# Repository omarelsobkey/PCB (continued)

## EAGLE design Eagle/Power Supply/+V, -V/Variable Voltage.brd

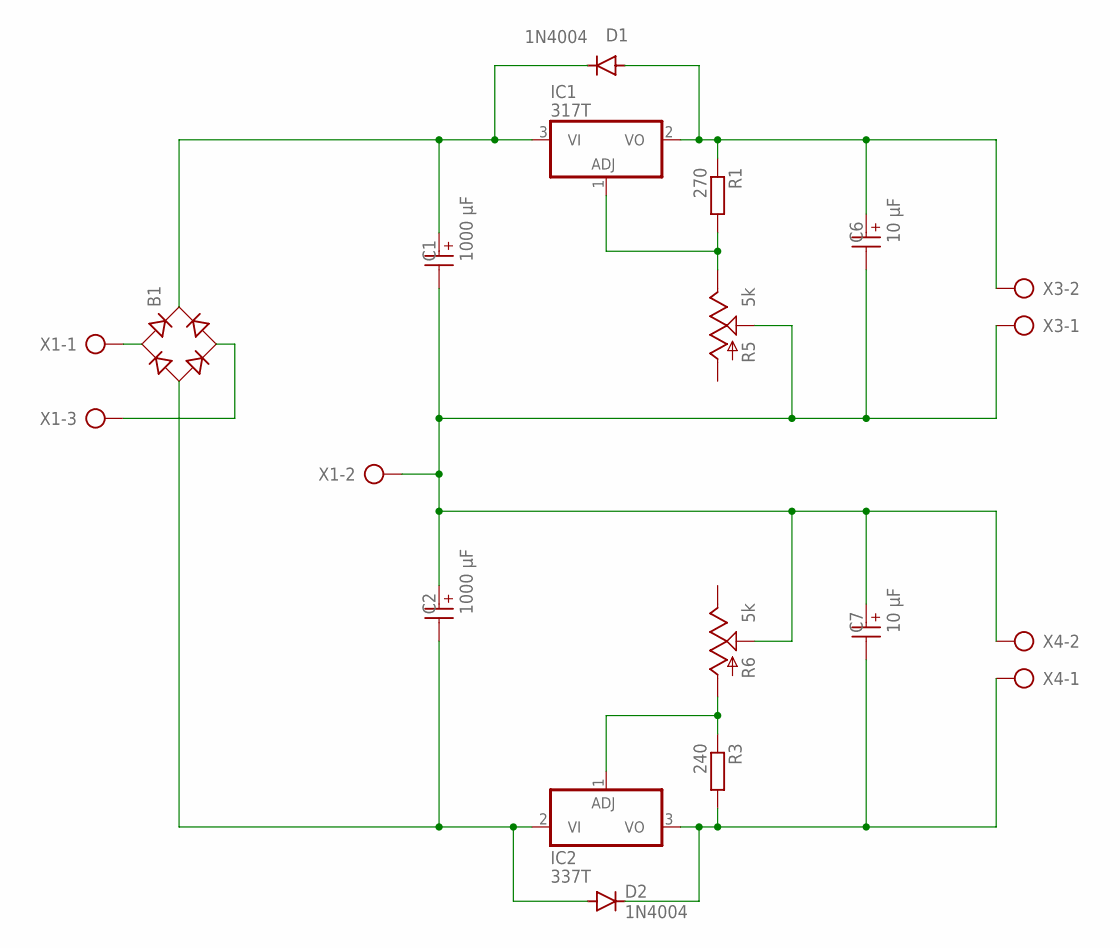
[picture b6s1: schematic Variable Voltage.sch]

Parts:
B1: RB1A
C1, C2: 1000 µF; WCAP-ATG8_10X12.5(DXL)
C6, C7: 10 µF; WCAP-ATG8_5X11(DXL)
D1, D2: 1N4004; DO41-10
IC1: 317T; TO220H
IC2: 337T; TO220H
R1: 270; 0204/7
R3: 240; 0204/7
R5, R6: 5k; CA9V
X1: AK300/3
X3, X4: AK300/2

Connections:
GND: C1.2 (-), C2.1 (+), C6.2 (-), C7.1 (+), R5.S, R6.S, X1.2, X3.1, X4.2
unnamed: B1.AC1, X1.1
unnamed: B1.AC2, X1.3
unnamed: B1.+, C1.1 (+), D1.C, IC1.3 (VI)
unnamed: B1.-, C2.2 (-), D2.A, IC2.2 (VI)
unnamed: IC2.1 (ADJ), R3.1, R6.A
unnamed: C7.2 (-), D2.C, IC2.3 (VO), R3.2, X4.1
unnamed: C6.1 (+), D1.A, IC1.2 (VO), R1.1, X3.2
unnamed: IC1.1 (ADJ), R1.2, R5.E

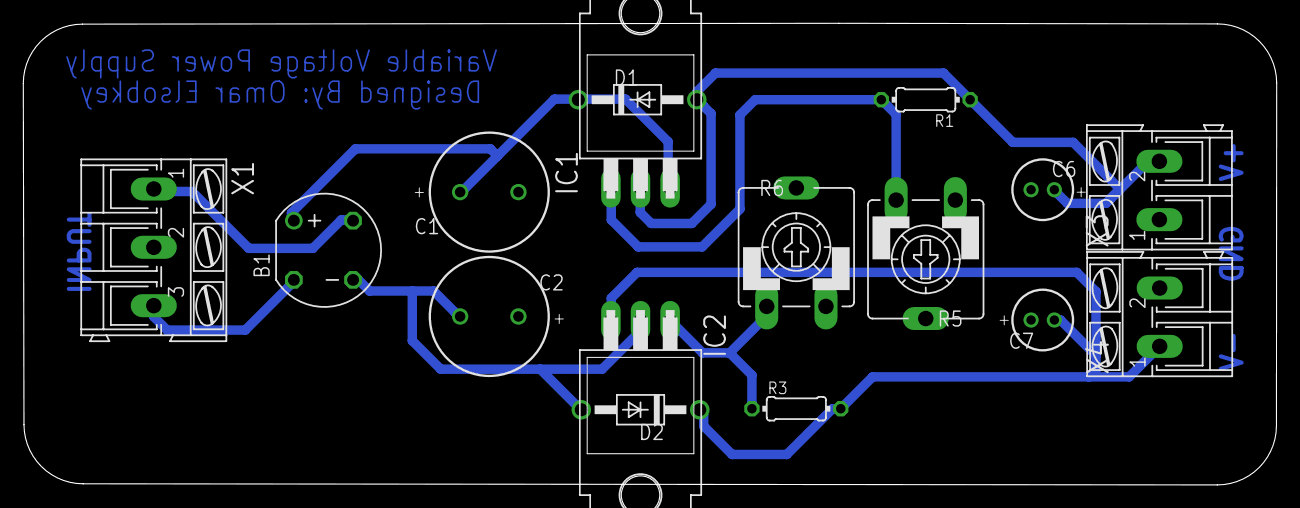
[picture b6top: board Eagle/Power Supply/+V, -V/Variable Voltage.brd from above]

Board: 2 copper layers, 107.5 x 39.6 mm, 16 parts (0 on the bottom side), 9 nets.

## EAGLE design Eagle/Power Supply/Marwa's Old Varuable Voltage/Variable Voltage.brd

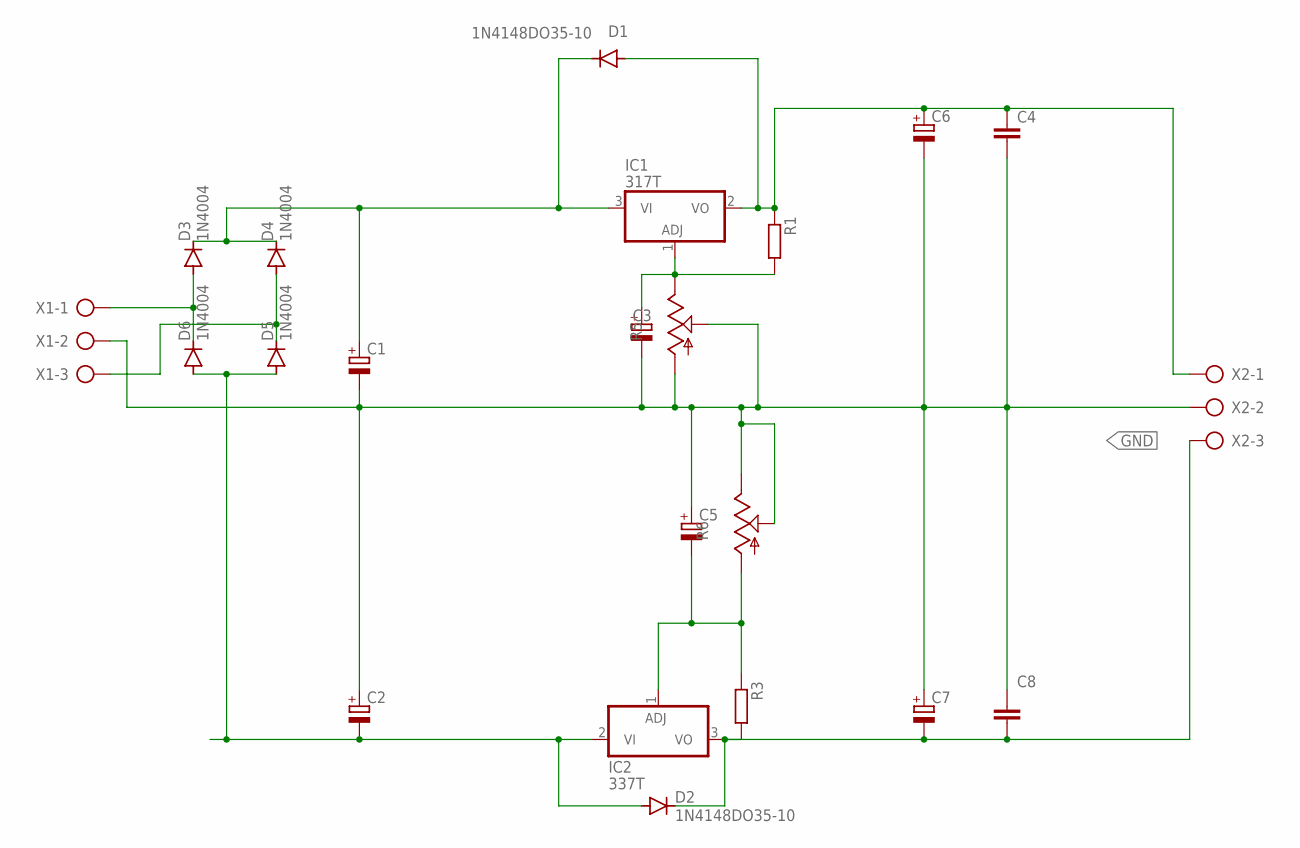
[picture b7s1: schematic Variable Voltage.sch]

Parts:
C1, C2: CPOL-EUE5-8.5; E5-8,5
C3, C5: CPOL-EUE2-4; E2-4
C4, C8: C2,5-3; C2.5-3
C6, C7: CPOL-EUE2.5-4V; E2,5RE
D1, D2: 1N4148DO35-10; DO35-10
D3, D4, D5, D6: 1N4004; DO41-10
IC1: 317T; TO220H
IC2: 337T; TO220H
R1, R3: R-EU_0204/7; 0204/7
R5, R6: TRIM_US-B25V; B25V
X1, X2: AK300/3

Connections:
GND: C1.-, C2.+, C3.-, C4.2, C5.+, C6.-, C7.+, C8.1, R5.A, R5.S, R6.E, R6.S, X1.2, X2.2
unnamed: D3.A, D6.C, X1.1
unnamed: D4.A, D5.C, X1.3
unnamed: C1.+, D1.C, D3.C, D4.C, IC1.3 (VI)
unnamed: C2.-, D2.A, D5.A, D6.A, IC2.2 (VI)
unnamed: C3.+, IC1.1 (ADJ), R1.2, R5.E
unnamed: C5.-, IC2.1 (ADJ), R3.1, R6.A
unnamed: C4.1, C6.+, D1.A, IC1.2 (VO), R1.1, X2.1
unnamed: C7.-, C8.2, D2.C, IC2.3 (VO), R3.2, X2.3

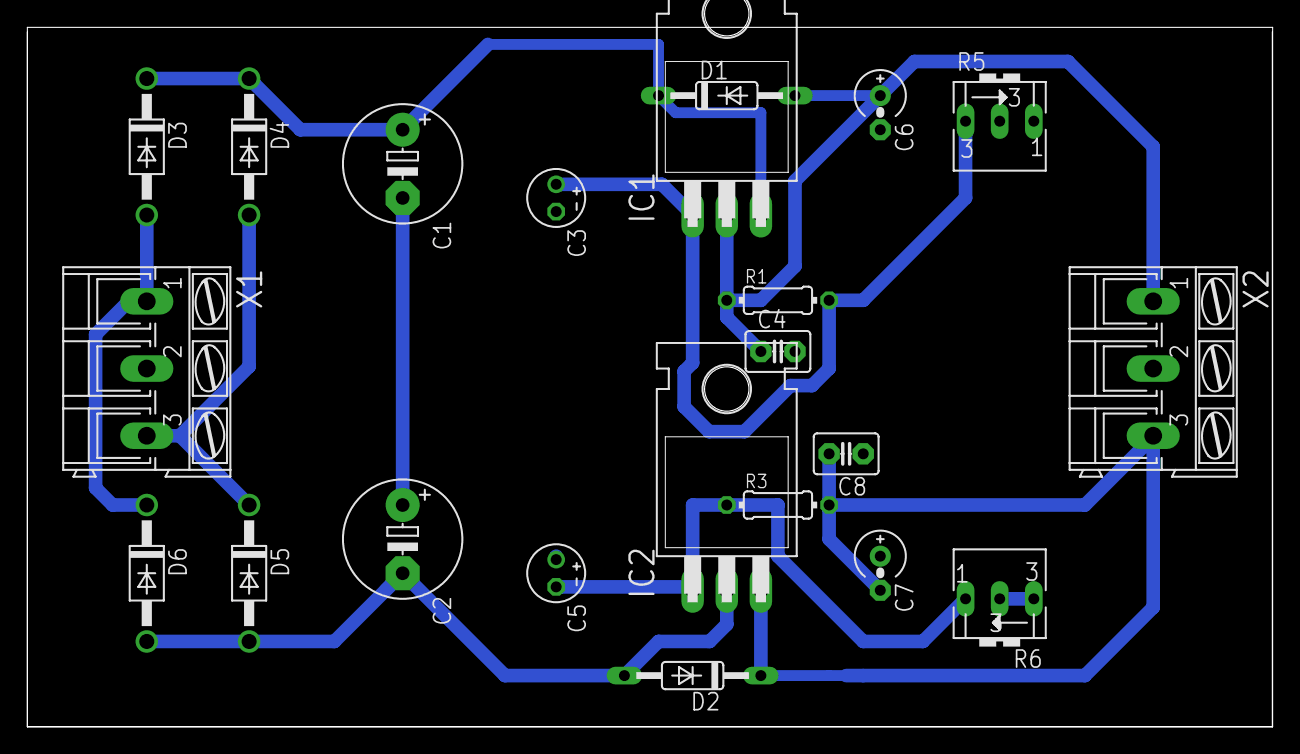
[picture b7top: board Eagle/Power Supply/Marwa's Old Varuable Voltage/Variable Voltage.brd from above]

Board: 2 copper layers, 92.7 x 52.1 mm, 22 parts (0 on the bottom side), 9 nets.

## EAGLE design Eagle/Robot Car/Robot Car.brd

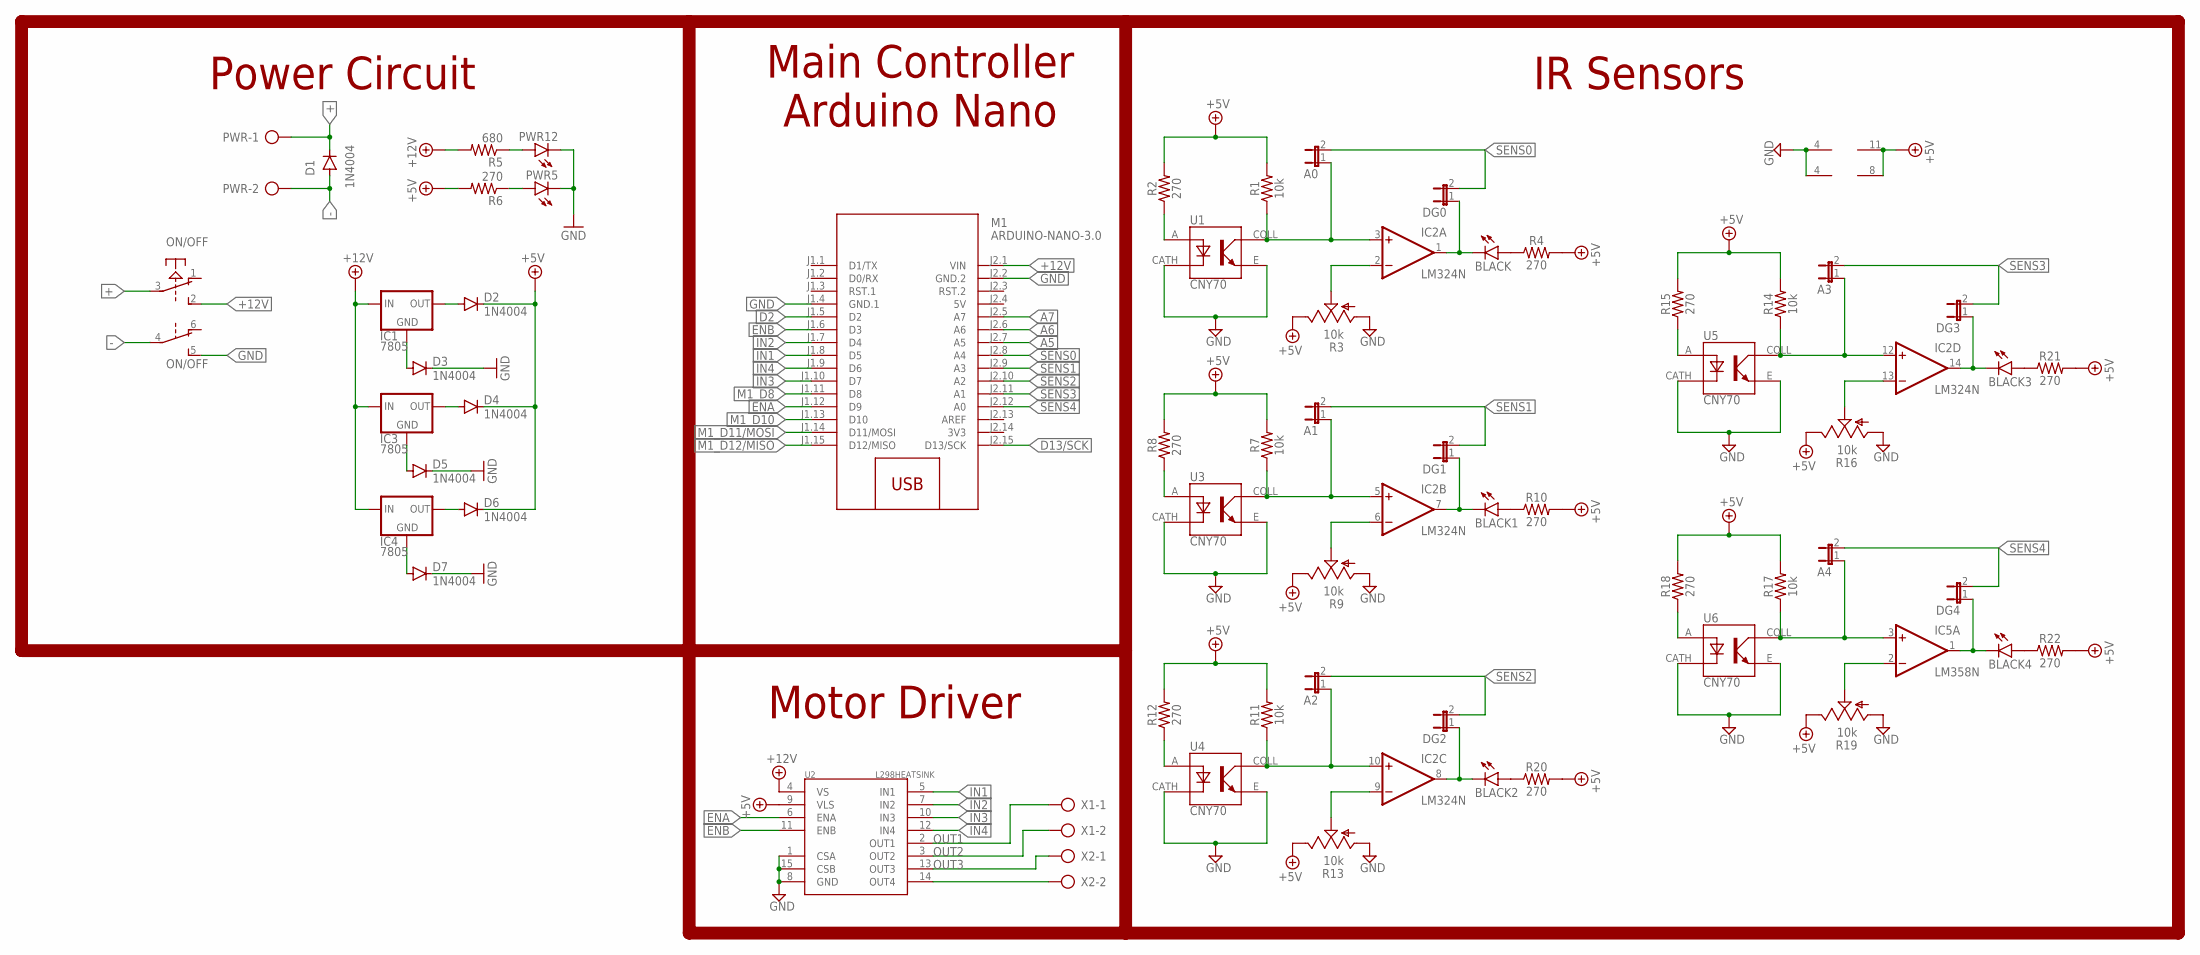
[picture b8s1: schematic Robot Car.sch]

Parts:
A0, A1, A2, A3, A4: JP1E; JP1
BLACK, BLACK1, BLACK2, BLACK3, BLACK4: LED3MM
D1, D2, D3, D4, D5, D6, D7: 1N4004; DO41-10
DG0, DG1, DG2, DG3, DG4: JP1E; JP1
IC1, IC3, IC4: 7805; 78XXS
IC2: LM324N; DIL14
IC5: LM358N; DIL08
M1: ARDUINO-NANO-3.0
ON/OFF: PVA2R
PWR: AK500/2-H
PWR5, PWR12: LED3MM
R1, R7, R11, R14, R17: 10k; AXIAL-0.3
R2, R4, R6, R8, R10, R12, R15, R18, R20, R21, R22: 270; AXIAL-0.3
R3, R9, R13, R16, R19: 10k; CA6V
R5: 680; AXIAL-0.3
U1, U3, U4, U5, U6: CNY70; DIPS254W50P254L710H600Q4
U2: L298HEATSINK; MULTIWATT15_6400BGHEATSINK
X1, X2: AK500/2-H

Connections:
3V3: M1.J2.14 (3V3)
5V: M1.J2.4 (5V)
+: D1.C, ON/OFF.3, PWR.1
+5V: D2.C, D4.C, D6.C, IC2.11 (V-), IC5.8 (V+), R1.P$2 (2), R2.P$2 (2), R3.E, R4.P$2 (2), R6.P$2 (2), R7.P$2 (2), R8.P$2 (2), R9.E, R10.P$2 (2), R11.P$2 (2), R12.P$2 (2), R13.E, R14.P$2 (2), R15.P$2 (2), R16.E, R17.P$2 (2), R18.P$2 (2), R19.E, R20.P$2 (2), R21.P$2 (2), R22.P$2 (2), U2.9 (VLS)
+12V: IC1.IN, IC3.IN, IC4.IN, M1.J2.1 (VIN), ON/OFF.2 (S), R5.P$2 (2), U2.4 (VS)
-: D1.A, ON/OFF.4, PWR.2
A5: M1.J2.7 (A5)
A6: M1.J2.6 (A6)
A7: M1.J2.5 (A7)
D2: M1.J1.5 (D2)
D13/SCK: M1.J2.15 (D13/SCK)
ENA: M1.J1.12 (D9), U2.6 (ENA)
ENB: M1.J1.6 (D3), U2.11 (ENB)
GND: D3.C, D5.C, D7.C, IC2.4 (V+), IC5.4 (V-), M1.J1.4 (GND.1), M1.J2.2 (GND.2), ON/OFF.5 (S), PWR5.K (C), PWR12.K (C), R3.A, R9.A, R13.A, R16.A, R19.A, U1.CATH, U1.E, U2.1 (CSA), U2.8 (GND), U2.15 (CSB), U3.CATH, U3.E, U4.CATH, U4.E, U5.CATH, U5.E, U6.CATH, U6.E
IN1: M1.J1.8 (D5), U2.5 (IN1)
IN2: M1.J1.7 (D4), U2.7 (IN2)
IN3: M1.J1.10 (D7), U2.10 (IN3)
IN4: M1.J1.9 (D6), U2.12 (IN4)
M1_D8: M1.J1.11 (D8)
M1_D10: M1.J1.13 (D10)
M1_D11/MOSI: M1.J1.14 (D11/MOSI)
M1_D12/MISO: M1.J1.15 (D12/MISO)
unnamed: R2.P$1 (1), U1.A
unnamed: PWR12.A, R5.P$1 (1)
unnamed: IC2.2 (-IN), R3.S
unnamed: PWR5.A, R6.P$1 (1)
unnamed: BLACK.A, R4.P$1 (1)
unnamed: D7.A, IC4.GND
unnamed: D5.A, IC3.GND
unnamed: D3.A, IC1.GND
unnamed: D2.A, IC1.OUT
unnamed: D6.A, IC4.OUT
unnamed: D4.A, IC3.OUT
unnamed: R8.P$1 (1), U3.A
unnamed: IC2.6 (-IN), R9.S
unnamed: BLACK1.A, R10.P$1 (1)
unnamed: R12.P$1 (1), U4.A
unnamed: IC2.9 (-IN), R13.S
unnamed: R15.P$1 (1), U5.A
unnamed: IC2.13 (-IN), R16.S
unnamed: R18.P$1 (1), U6.A
unnamed: IC5.2 (-IN), R19.S
unnamed: BLACK2.A, R20.P$1 (1)
unnamed: BLACK3.A, R21.P$1 (1)
unnamed: BLACK4.A, R22.P$1 (1)
unnamed: A4.1, IC5.3 (+IN), R17.P$1 (1), U6.COLL
unnamed: BLACK4.K (C), DG4.1, IC5.1 (OUT)
unnamed: BLACK3.K (C), DG3.1, IC2.14 (OUT)
unnamed: A3.1, IC2.12 (+IN), R14.P$1 (1), U5.COLL
unnamed: BLACK.K (C), DG0.1, IC2.1 (OUT)
unnamed: A0.1, IC2.3 (+IN), R1.P$1 (1), U1.COLL
unnamed: A1.1, IC2.5 (+IN), R7.P$1 (1), U3.COLL
unnamed: BLACK1.K (C), DG1.1, IC2.7 (OUT)
unnamed: A2.1, IC2.10 (+IN), R11.P$1 (1), U4.COLL
unnamed: BLACK2.K (C), DG2.1, IC2.8 (OUT)
unnamed: U2.14 (OUT4), X2.2
OUT1: U2.2 (OUT1), X1.1
OUT2: U2.3 (OUT2), X1.2
OUT3: U2.13 (OUT3), X2.1
SENS0: A0.2, DG0.2, M1.J2.8 (A4)
SENS1: A1.2, DG1.2, M1.J2.9 (A3)
SENS2: A2.2, DG2.2, M1.J2.10 (A2)
SENS3: A3.2, DG3.2, M1.J2.11 (A1)
SENS4: A4.2, DG4.2, M1.J2.12 (A0)

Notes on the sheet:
Power Circuit
Main Controller Arduino Nano
IR Sensors
Motor Driver

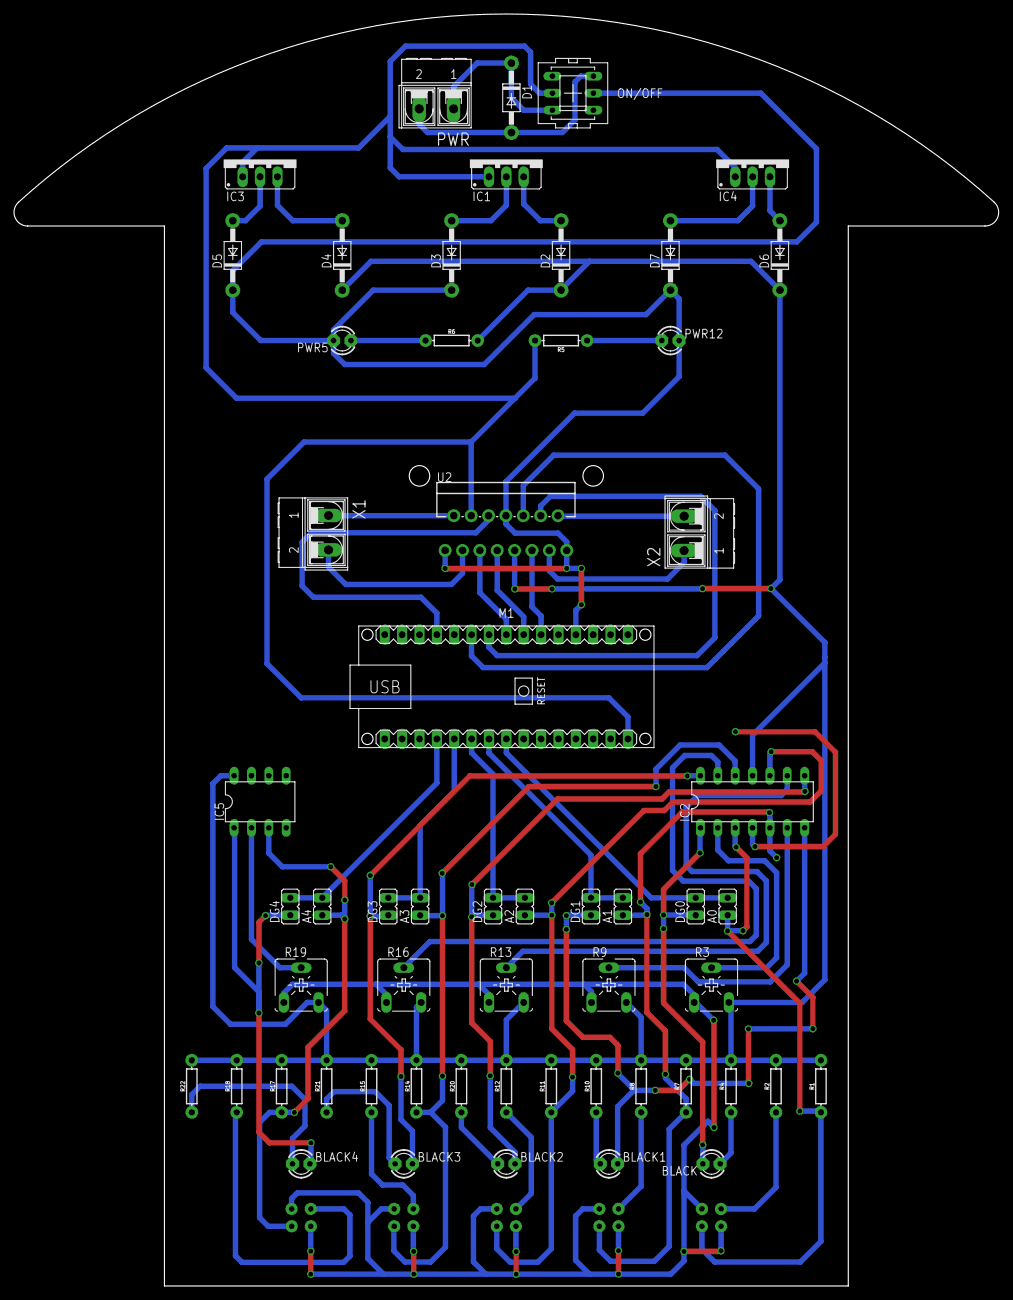
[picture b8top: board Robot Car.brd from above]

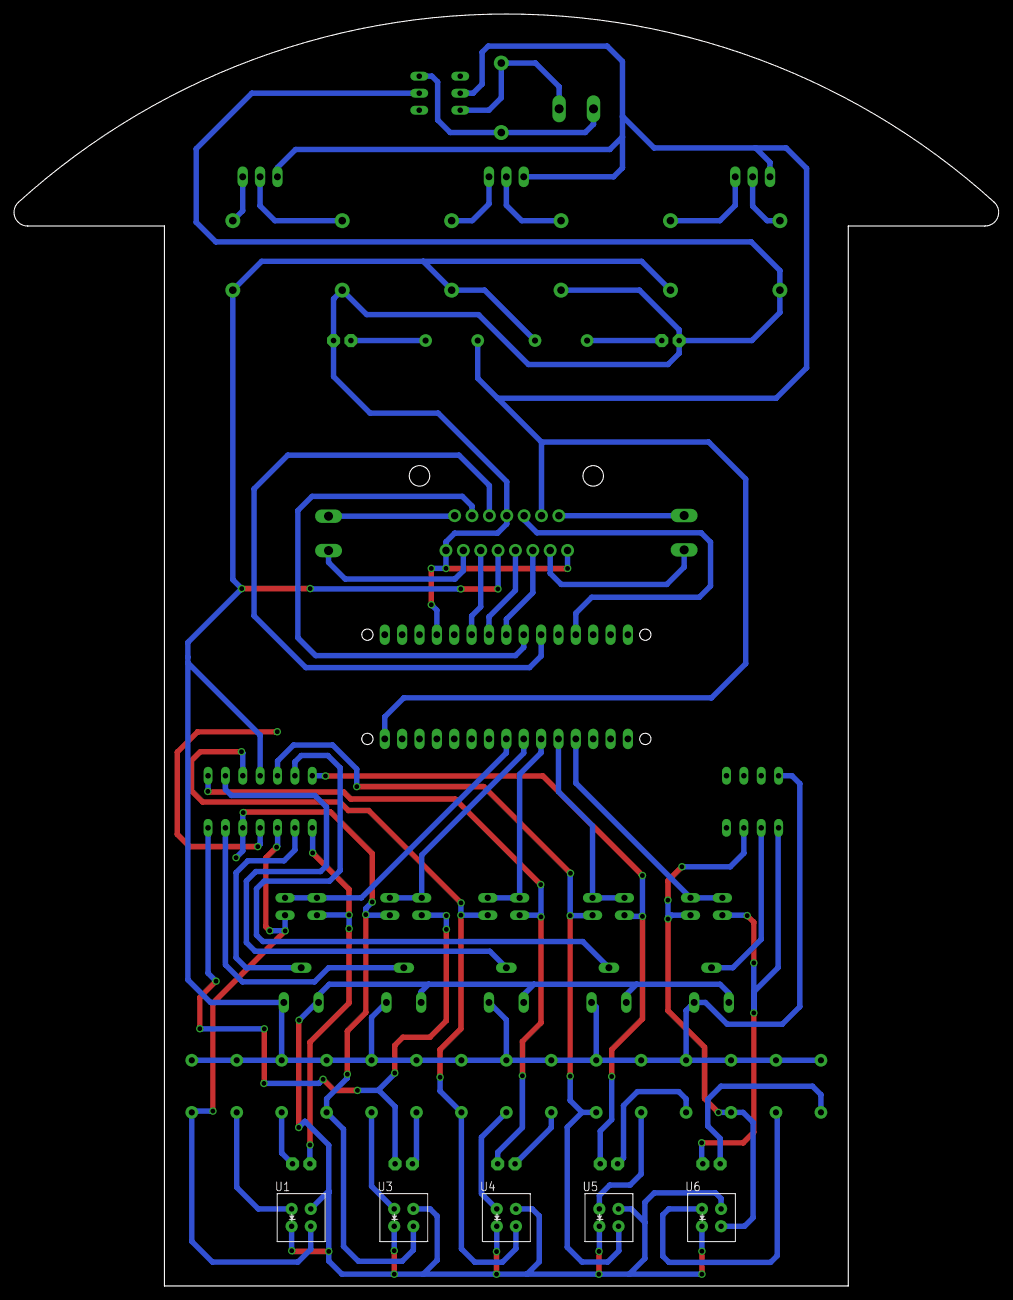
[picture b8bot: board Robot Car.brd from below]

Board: 2 copper layers, 144.0 x 186.0 mm, 62 parts (5 on the bottom side), 53 nets.
